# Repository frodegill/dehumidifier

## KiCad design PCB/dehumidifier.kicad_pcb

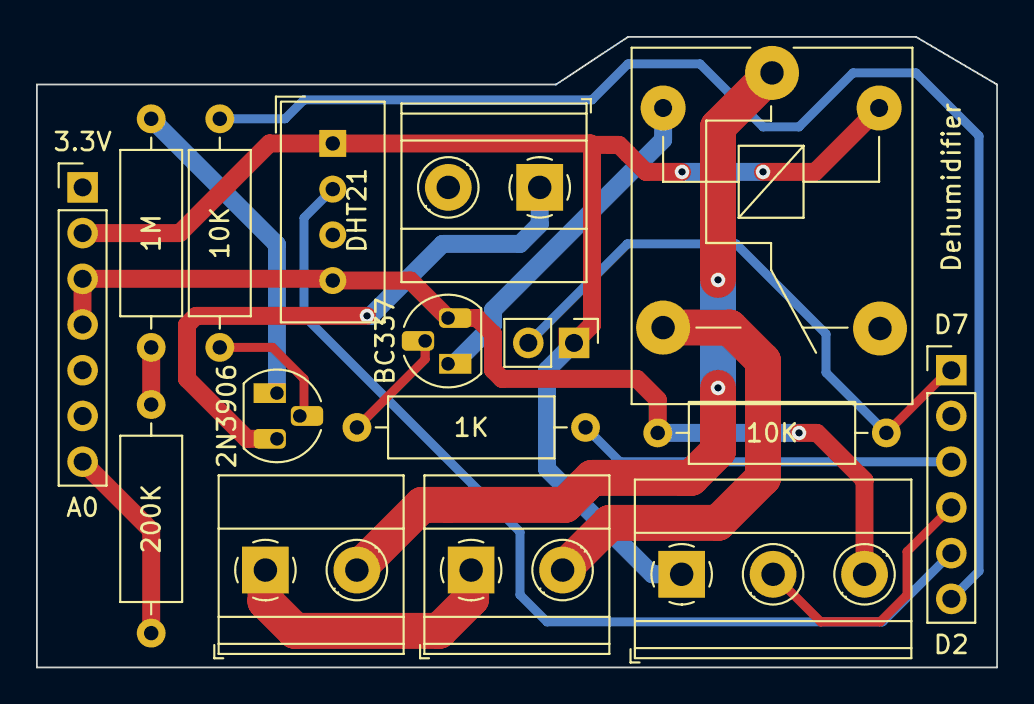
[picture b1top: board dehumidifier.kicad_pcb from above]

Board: 2 copper layers, 53.3 x 35.0 mm, 16 parts (0 on the bottom side), 17 nets.

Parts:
1K: R; R_Axial_DIN0309_L9.0mm_D3.2mm_P12.70mm_Horizontal
1M: 1M; R_Axial_DIN0309_L9.0mm_D3.2mm_P12.70mm_Horizontal
10K: 10K; R_Axial_DIN0309_L9.0mm_D3.2mm_P12.70mm_Horizontal
200K: 200K; R_Axial_DIN0309_L9.0mm_D3.2mm_P12.70mm_Horizontal
J1, J2, J15: Conn_01x02_Male; TerminalBlock_Phoenix_MKDS-1,5-2-5.08_1x02_P5.08mm_Horizont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
J3: Conn_01x03_Male; TerminalBlock_Phoenix_MKDS-1,5-3-5.08_1x03_P5.08mm_Horizont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
J4: Conn_01x02_Male; PinHeader_1x02_P2.54mm_Vertical
J14: Conn_01x07_Male; PinHeader_1x07_P2.54mm_Vertical
J16: Conn_01x06_Male; PinHeader_1x06_P2.54mm_Vertical
K1: SANYOU_SRD_Form_C; Relay_SPDT_SANYOU_SRD_Series_Form_C
Q1: 2N3906; TO-92_HandSolder
Q2: BC337; TO-92_HandSolder
R2: 10K; R_Axial_DIN0309_L9.0mm_D3.2mm_P12.70mm_Horizontal
U1: DHT11; Aosong_DHT11_5.5x12.0_P2.54mm

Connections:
+5V: J3.1, J4.1, J14.2, K1.5, U1.1 (VCC)
GND: J3.3, J14.3, J14.4, Q2.3 (E), R2.1, U1.4 (GND)
unnamed: J1.1, J2.1
unnamed: J1.2, K1.1
unnamed: J2.2, K1.3
unnamed: 200K.1, J14.7
unnamed: J15.1, Q1.3 (C)
unnamed: J4.2, J16.1, R2.2
unnamed: 1K.2, J16.3
unnamed: J3.2, J16.4
unnamed: J16.5, U1.2 (IO)
unnamed: 10K.1, J16.6
unnamed: K1.2, Q2.1 (C)
unnamed: 1M.1, Q1.1 (E)
unnamed: 10K.2, Q1.2 (B)
unnamed: 1K.1, Q2.2 (B)
unnamed: 1M.2, 200K.2

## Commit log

2023-03-20 Added source code
2023-03-21 Added KiCAD files
